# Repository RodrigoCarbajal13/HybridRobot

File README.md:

# HybridRobot
Github created by Mechatronic Engineerings from Peru

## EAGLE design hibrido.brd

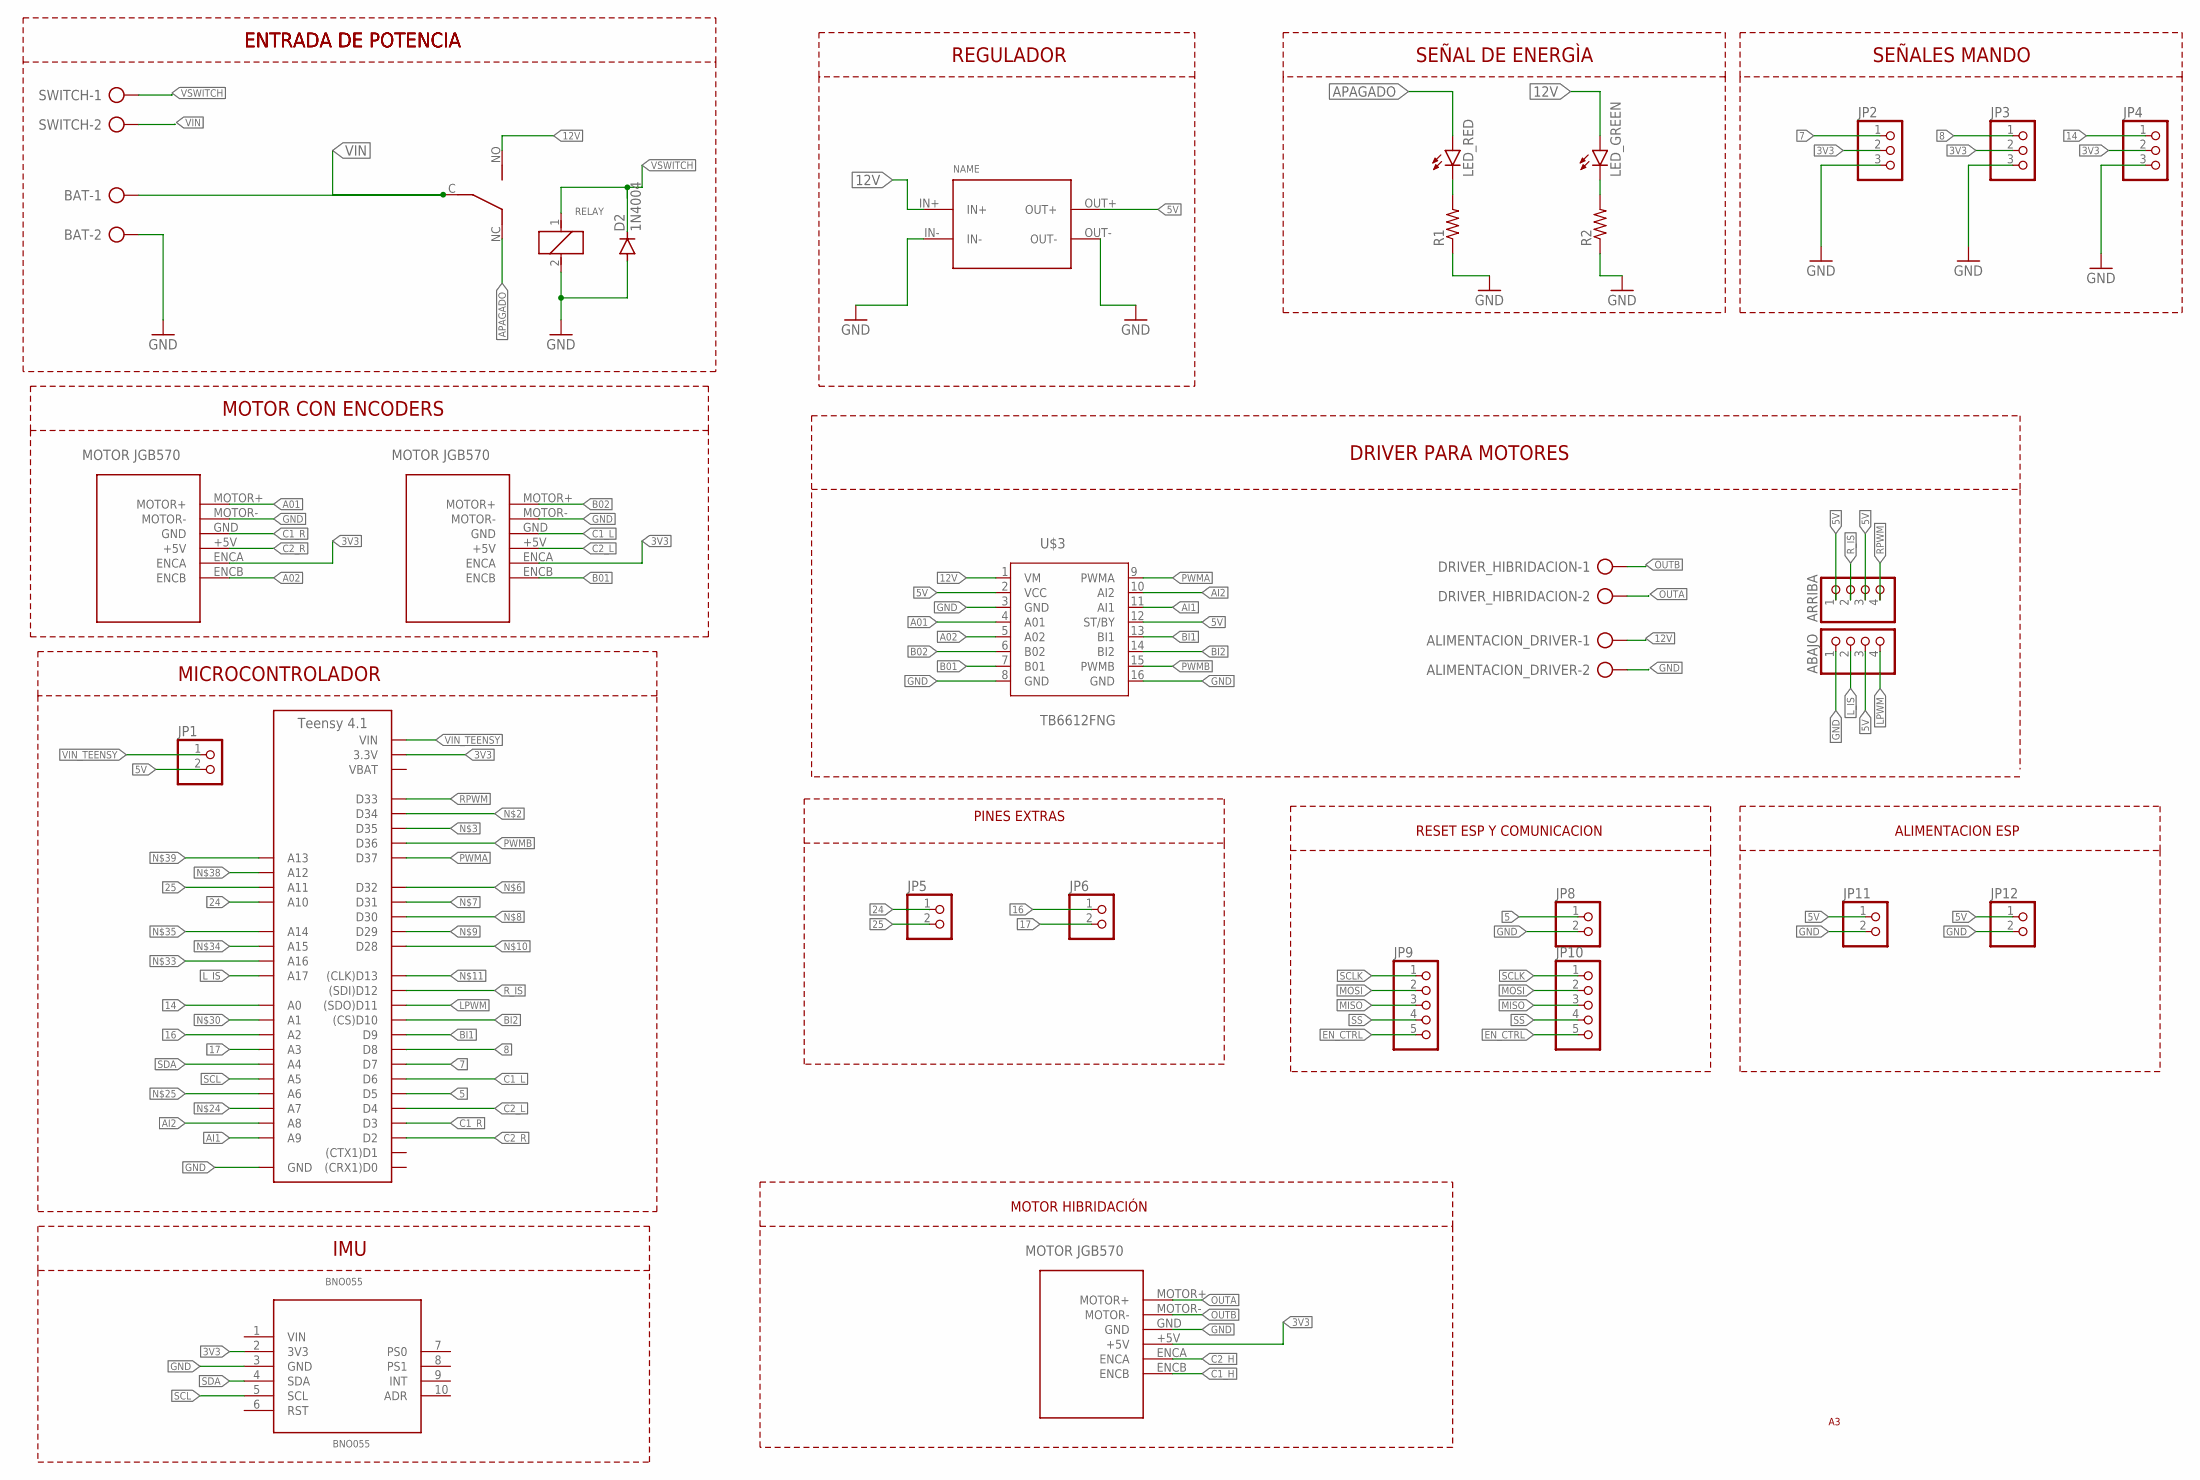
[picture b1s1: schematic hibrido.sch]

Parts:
A1: TEENSY_4.1; TEENSY_LONG_EXT
ABAJO: PINHD-1X4; 1X04
ALIMENTACION_DRIVER: AK500/2-H
ARRIBA: PINHD-1X4; 1X04
BAT: AK500/2-H
BNO055: BNO055
D2: 1N4004; DO41-10
DRIVER_HIBRIDACION: AK500/2-H
JP1, JP5, JP6, JP8, JP11, JP12: PINHD-1X2; 1X02
JP2, JP3, JP4: PINHD-1X3; 1X03
JP9, JP10: PINHD-1X5; 1X05
LED_GREEN: LED5MM
LED_RED: LED5MM
MOTOR1, MOTOR3, MOTOR5: MOTOR_JGB370
R1, R2: R-US_0207/10; 0207/10
REG: CP8-ADJ
RELAY: RELAY12V
SWITCH: AK500/2-H
U$3: TB6612FNG

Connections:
3V3: A1.3V3 (3.3V), A1.3V3@2 (3.3V), A1.3V3@3 (3.3V), BNO055.2 (3V3), JP2.2, JP3.2, JP4.2, MOTOR1.+5V, MOTOR3.ENCA, MOTOR5.ENCA
5: A1.D5, JP8.1
5V: ABAJO.3, ARRIBA.1, ARRIBA.3, JP1.2, JP11.1, JP12.1, REG.OUT+, U$3.2 (VCC), U$3.12 (ST/BY)
7: A1.D7, JP2.1
8: A1.D8, JP3.1
12V: ALIMENTACION_DRIVER.1, LED_GREEN.A, REG.IN+, RELAY.NO, U$3.1 (VM)
14: A1.D14 (A0), JP4.1
16: A1.D16 (A2), JP6.1
17: A1.D17 (A3), JP6.2
24: A1.D24 (A10), JP5.1
25: A1.D25 (A11), JP5.2
A01: MOTOR3.MOTOR+, U$3.4 (A01)
A02: MOTOR3.ENCB, U$3.5 (A02)
AI1: A1.D23 (A9), U$3.11 (AI1)
AI2: A1.D22 (A8), U$3.10 (AI2)
APAGADO: LED_RED.A, RELAY.NC
B01: MOTOR5.ENCB, U$3.7 (B01)
B02: MOTOR5.MOTOR+, U$3.6 (B02)
BI1: A1.D9, U$3.13 (BI1)
BI2: A1.D10 ((CS)D10), U$3.14 (BI2)
C1_H: MOTOR1.ENCB
C1_L: A1.D6, MOTOR5.GND
C1_R: A1.D3, MOTOR3.GND
C2_H: MOTOR1.ENCA
C2_L: A1.D4, MOTOR5.+5V
C2_R: A1.D2, MOTOR3.+5V
EN_CTRL: JP9.5, JP10.5
GND: A1.AGND/GND (GND), A1.GND, A1.GND@2 (GND), ABAJO.1, ALIMENTACION_DRIVER.2, BAT.2, BNO055.3 (GND), D2.A, JP2.3, JP3.3, JP4.3, JP8.2, JP11.2, JP12.2, MOTOR1.GND, MOTOR3.MOTOR-, MOTOR5.MOTOR-, R1.1, R2.1, REG.IN-, REG.OUT-, RELAY.2, U$3.3 (GND), U$3.8 (GND), U$3.16 (GND)
LPWM: A1.D11 ((SDO)D11), ABAJO.4
L_IS: A1.D41 (A17), ABAJO.2
MISO: JP9.3, JP10.3
MOSI: JP9.2, JP10.2
unnamed: LED_RED.K (C), R1.2
unnamed: LED_GREEN.K (C), R2.2
OUTA: DRIVER_HIBRIDACION.2, MOTOR1.MOTOR+
OUTB: DRIVER_HIBRIDACION.1, MOTOR1.MOTOR-
PWMA: A1.D37, U$3.9 (PWMA)
PWMB: A1.D36, U$3.15 (PWMB)
RPWM: A1.D33, ARRIBA.4
R_IS: A1.D12 ((SDI)D12), ARRIBA.2
SCL: A1.D19 (A5), BNO055.5 (SCL)
SCLK: JP9.1, JP10.1
SDA: A1.D18 (A4), BNO055.4 (SDA)
SS: JP9.4, JP10.4
VBAT: A1.VBAT
VIN: BAT.1, RELAY.C, SWITCH.2
VIN_TEENSY: A1.VIN, JP1.1
VSWITCH: D2.C, RELAY.1, SWITCH.1

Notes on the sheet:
MICROCONTROLADOR
IMU
ENTRADA DE POTENCIA
REGULADOR
SEÑAL DE ENERGÌA
MOTOR CON ENCODERS
DRIVER PARA MOTORES
MOTOR HIBRIDACIÓN
SEÑALES MANDO
PINES EXTRAS
RESET ESP Y COMUNICACION
ALIMENTACION ESP

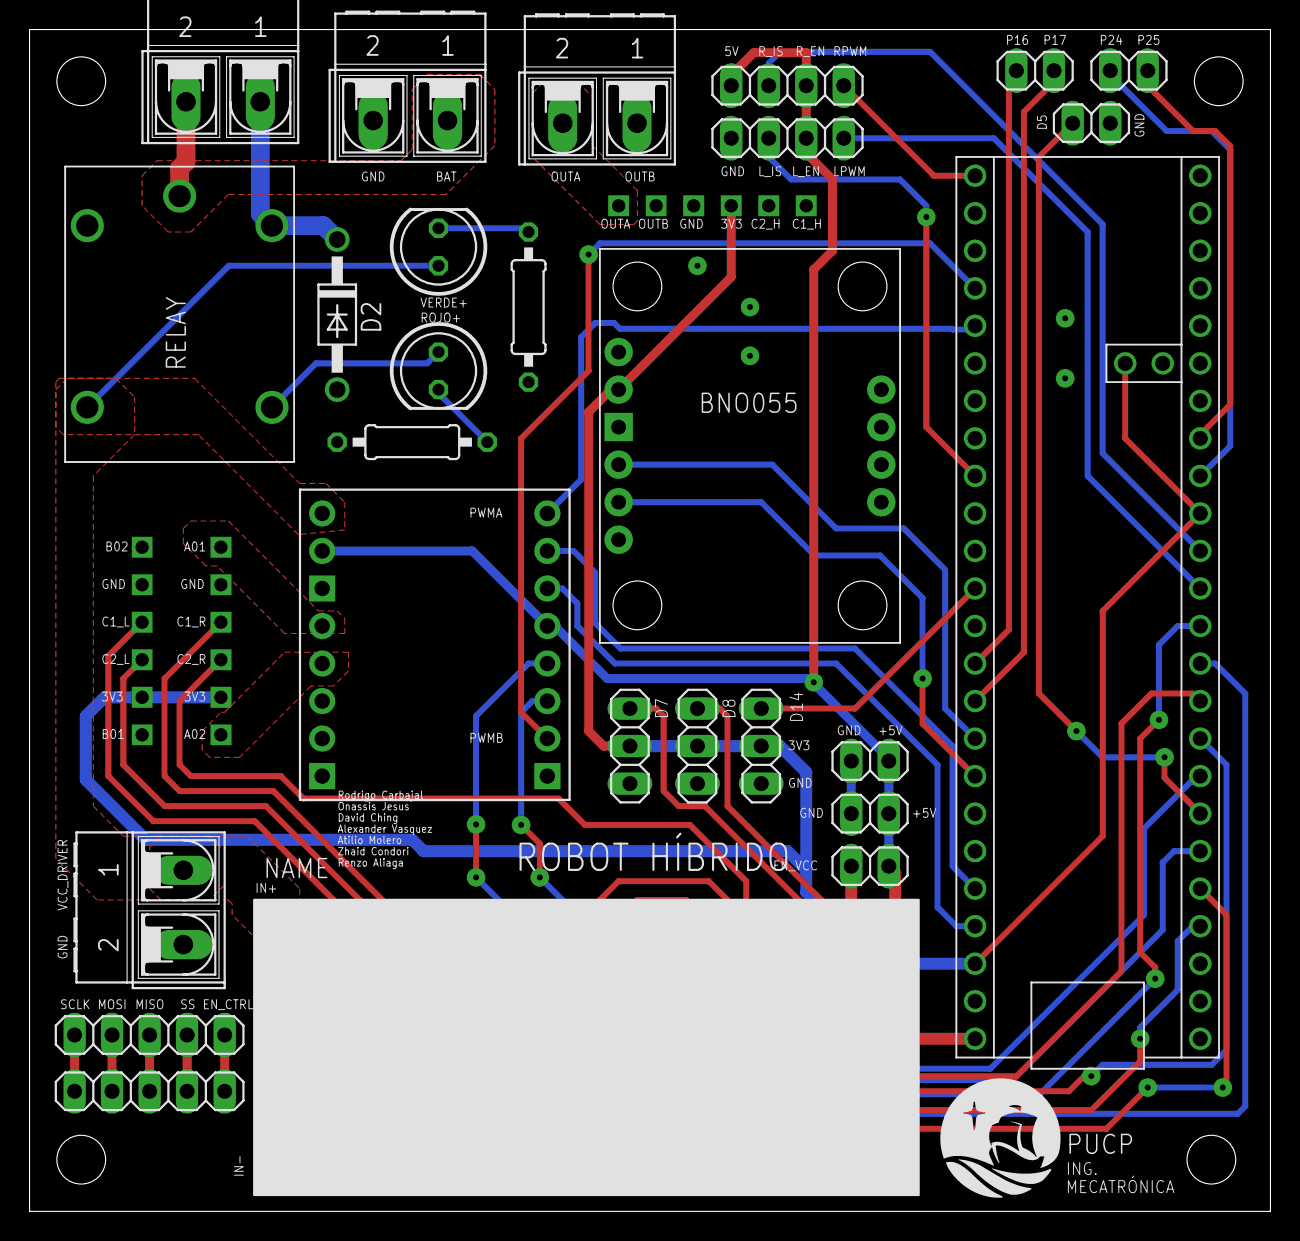
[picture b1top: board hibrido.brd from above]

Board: 2 copper layers, 84.0 x 80.0 mm, 30 parts (0 on the bottom side), 45 nets.

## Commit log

2025-11-04 Hybrid Robot PCB Base
2025-11-05 Primer avance
2025-11-05 Hibrido casi terminado, sin considerar comunicación entre ESPs
2025-11-05 cambios casi finales
2025-11-05 Archivos eliminados
2025-11-06 PCB antes del cambio del drill vias
2025-11-06 Elaboracion de tags sin modificacion de vias
2025-11-06 Version final de la PCB, falta revisar por los demás
2025-11-07 Cambios finales con los nombres
    xd
